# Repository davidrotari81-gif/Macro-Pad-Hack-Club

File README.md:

# Macro-Pad-Hack-Club
This is my first time creating a macropad and also the first doing something like PCB, Coding, And design (it hurted like hell)

# Features 
it shows you the flags in asseto corsa competitione (ACC) using leds and the OLED display
it also can be used as a normal macropad

# Components 
9x SK6812 MINI-E LEDs
1x 0.91 inch OLED displays
12x MX-Style switches
12x Through-hole 1N4148 Diodes

# PCB 
Here is the picture of the PCB and the schemathics (i use 9 leds for showing flags from ACC)

# CAD

CAD design (is the worst part of the project cause i was running out of time 30/12/2025)

# Firmware
 I will use arduino because i ned the leds to colour by the color of the flags in ACC

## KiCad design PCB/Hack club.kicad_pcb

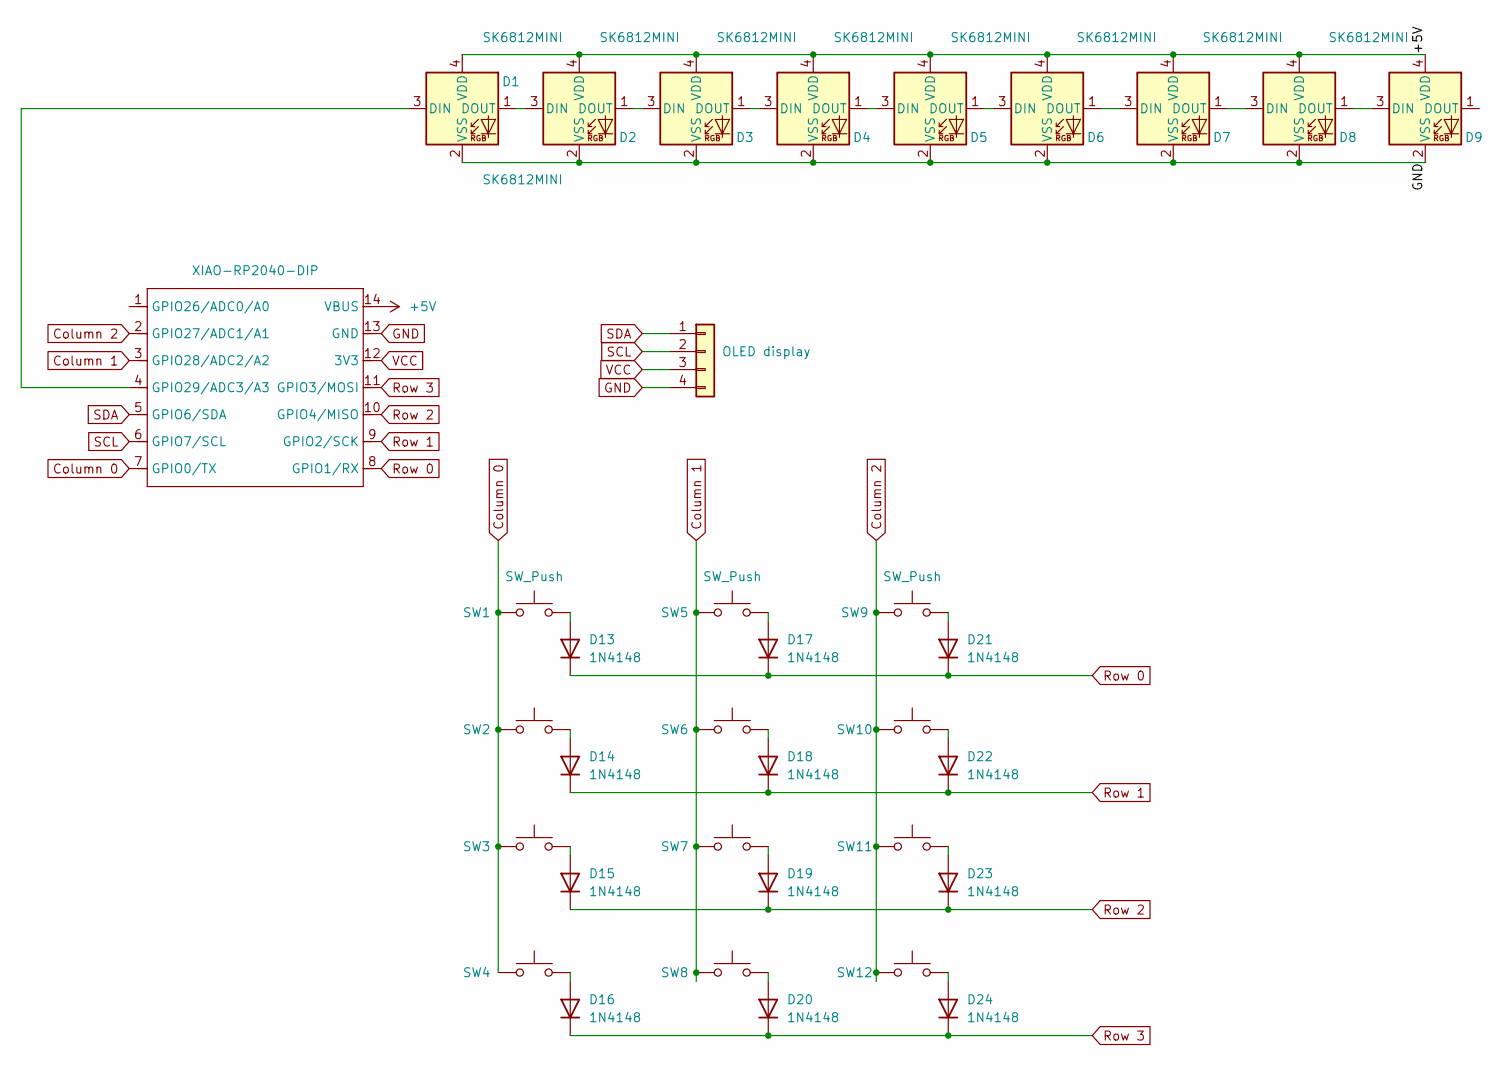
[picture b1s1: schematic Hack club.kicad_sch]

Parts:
D1, D2, D3, D4, D5, D6, D7, D8, D9: SK6812MINI; LED_SK6812MINI_PLCC4_3.5x3.5mm_P1.75mm
D13, D14, D15, D16, D17, D18, D19, D20, D21, D22, D23, D24: 1N4148; D_DO-35_SOD27_P7.62mm_Horizontal
J1: OLED display; PinHeader_1x04_P2.54mm_Vertical
SW1, SW2, SW3, SW4, SW5, SW6, SW7, SW8, SW9, SW10, SW11, SW12: SW_Push; SW_Cherry_MX_1.00u_PCB
U2: XIAO-RP2040-DIP

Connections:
+5V: D1.4 (VDD), D2.4 (VDD), D3.4 (VDD), D4.4 (VDD), D5.4 (VDD), D6.4 (VDD), D7.4 (VDD), D8.4 (VDD), D9.4 (VDD), U2.14 (VBUS)
Column 0: SW1.1, SW2.1, SW3.1, SW4.1, U2.7 (GPIO0/TX)
Column 1: SW5.1, SW6.1, SW7.1, SW8.1, U2.3 (GPIO28/ADC2/A2)
Column 2: SW9.1, SW10.1, SW11.1, SW12.1, U2.2 (GPIO27/ADC1/A1)
GND: D1.2 (VSS), D2.2 (VSS), D3.2 (VSS), D4.2 (VSS), D5.2 (VSS), D6.2 (VSS), D7.2 (VSS), D8.2 (VSS), D9.2 (VSS), J1.4, U2.13 (GND)
unnamed: D1.3 (DIN), U2.4 (GPIO29/ADC3/A3)
unnamed: D1.1 (DOUT), D2.3 (DIN)
unnamed: D2.1 (DOUT), D3.3 (DIN)
unnamed: D3.1 (DOUT), D4.3 (DIN)
unnamed: D4.1 (DOUT), D5.3 (DIN)
unnamed: D5.1 (DOUT), D6.3 (DIN)
unnamed: D6.1 (DOUT), D7.3 (DIN)
unnamed: D7.1 (DOUT), D8.3 (DIN)
unnamed: D8.1 (DOUT), D9.3 (DIN)
unnamed: D13.2 (A), SW1.2
unnamed: D14.2 (A), SW2.2
unnamed: D15.2 (A), SW3.2
unnamed: D16.2 (A), SW4.2
unnamed: D17.2 (A), SW5.2
unnamed: D18.2 (A), SW6.2
unnamed: D19.2 (A), SW7.2
unnamed: D20.2 (A), SW8.2
unnamed: D21.2 (A), SW9.2
unnamed: D22.2 (A), SW10.2
unnamed: D23.2 (A), SW11.2
unnamed: D24.2 (A), SW12.2
Row 0: D13.1 (K), D17.1 (K), D21.1 (K), U2.8 (GPIO1/RX)
Row 1: D14.1 (K), D18.1 (K), D22.1 (K), U2.9 (GPIO2/SCK)
Row 2: D15.1 (K), D19.1 (K), D23.1 (K), U2.10 (GPIO4/MISO)
Row 3: D16.1 (K), D20.1 (K), D24.1 (K), U2.11 (GPIO3/MOSI)
SCL: J1.2, U2.6 (GPIO7/SCL)
SDA: J1.1, U2.5 (GPIO6/SDA)
VCC: J1.3, U2.12 (3V3)

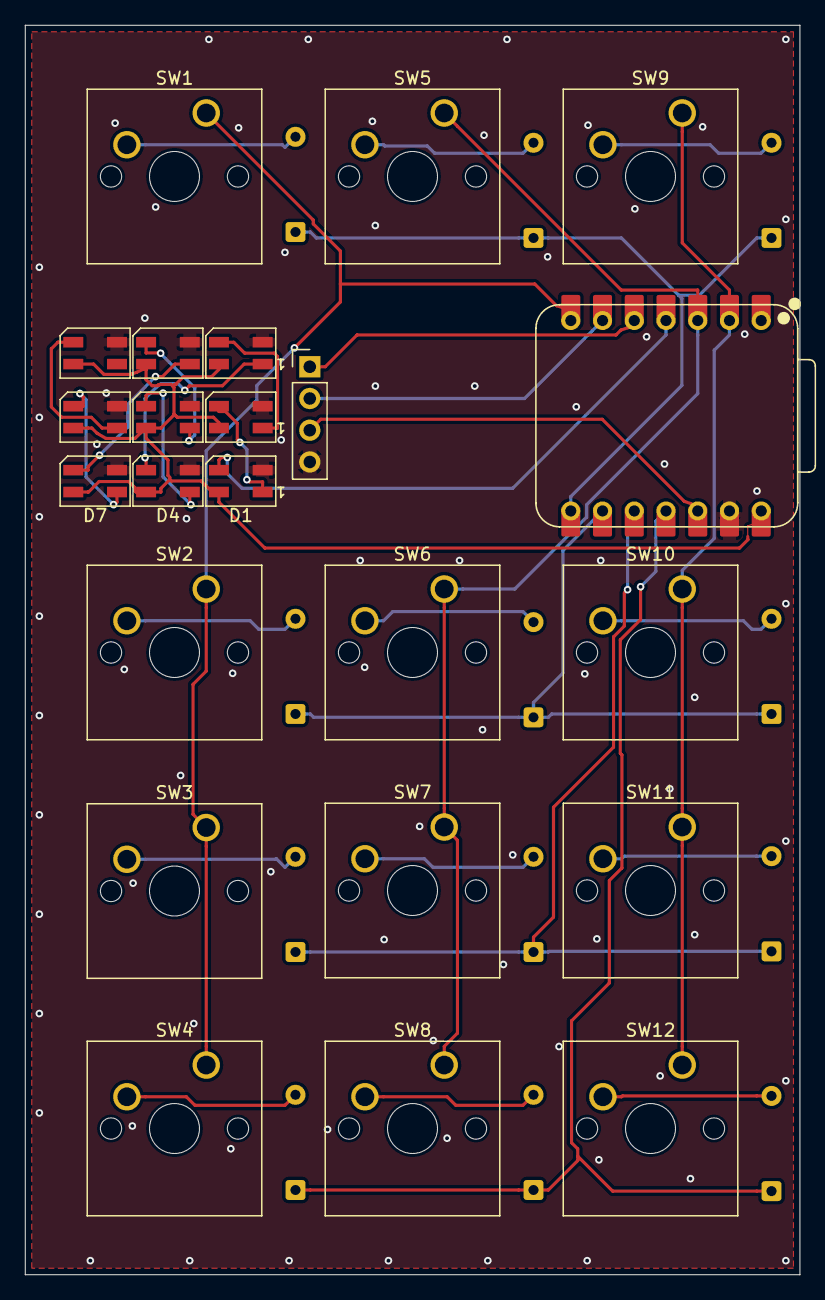
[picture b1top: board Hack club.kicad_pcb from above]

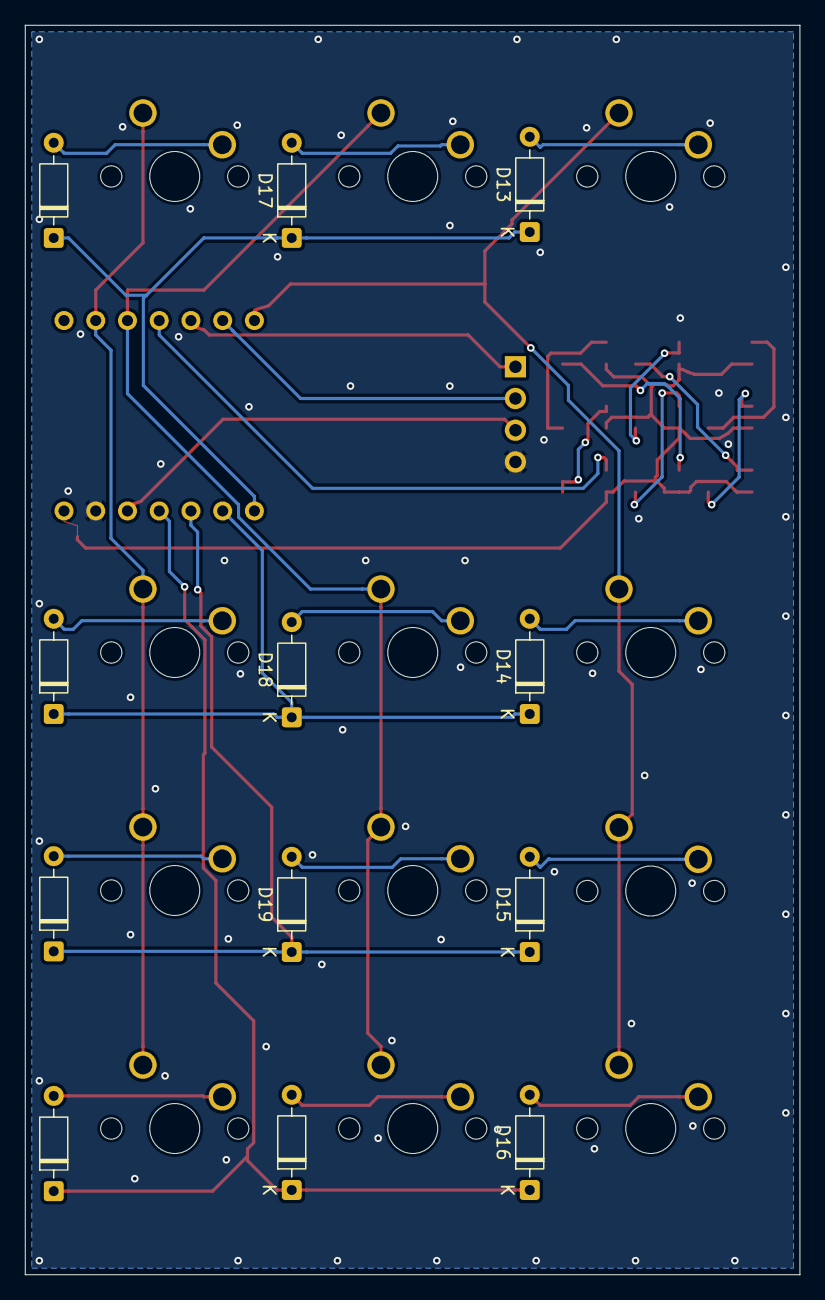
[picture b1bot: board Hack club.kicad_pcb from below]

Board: 2 copper layers, 62.0 x 100.0 mm, 35 parts (12 on the bottom side), 33 nets.

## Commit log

2025-12-30 README.md
2025-12-30 Create pcb
2025-12-30 Add files via upload
    Case PCB 1 is without assembling, Case PCB is assembeled and with de pcb
2025-12-30 Create Guide
2025-12-30 Rename Guide to Guide <-- READ
2025-12-30 Create Firmware (arduino)
2025-12-30 Update Firmware (arduino)
